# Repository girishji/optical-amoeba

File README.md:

# optical-amoeba
Single switch PCB for Gateron MX-style optical switches

See [pcb](https://github.com/girishji/optical-keyboard)

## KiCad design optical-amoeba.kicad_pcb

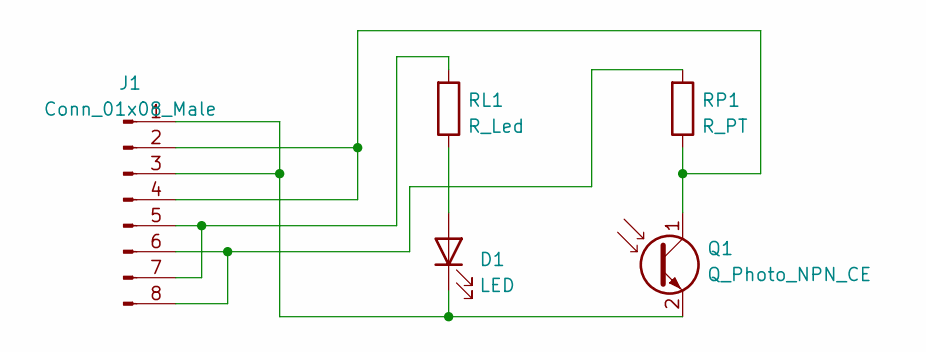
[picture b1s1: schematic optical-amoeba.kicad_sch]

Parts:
D1: LED; Everlight_IR_IR12-21C_TR8; JLC SMD_1.0x3.0x2.0
J1: Conn_01x08_Male; Gateron_Optical_Switch
Q1: Q_Photo_NPN_CE; Everlight_PT_PT12-21C_TR8; JLC SMD_1.0x3.0x2.0
RL1: R_Led; R_0603_1608Metric; JLC 0603-1608
RP1: R_PT; R_0805_2012Metric; JLC 0805-2012

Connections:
unnamed: D1.1 (K), J1.1, J1.3, Q1.2 (E)
unnamed: D1.2 (A), RL1.2
unnamed: J1.2, J1.4, Q1.1 (C), RP1.2
unnamed: J1.5, J1.7, RL1.1
unnamed: J1.6, J1.8, RP1.1

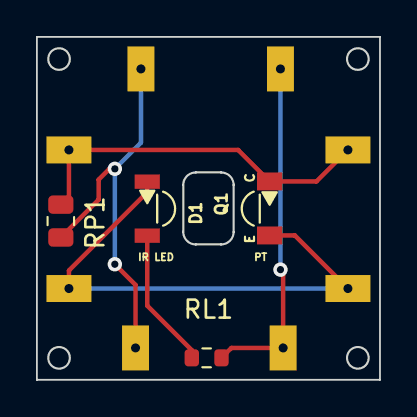
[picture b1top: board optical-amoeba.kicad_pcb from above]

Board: 2 copper layers, 19.1 x 19.0 mm, 5 parts (0 on the bottom side), 5 nets.

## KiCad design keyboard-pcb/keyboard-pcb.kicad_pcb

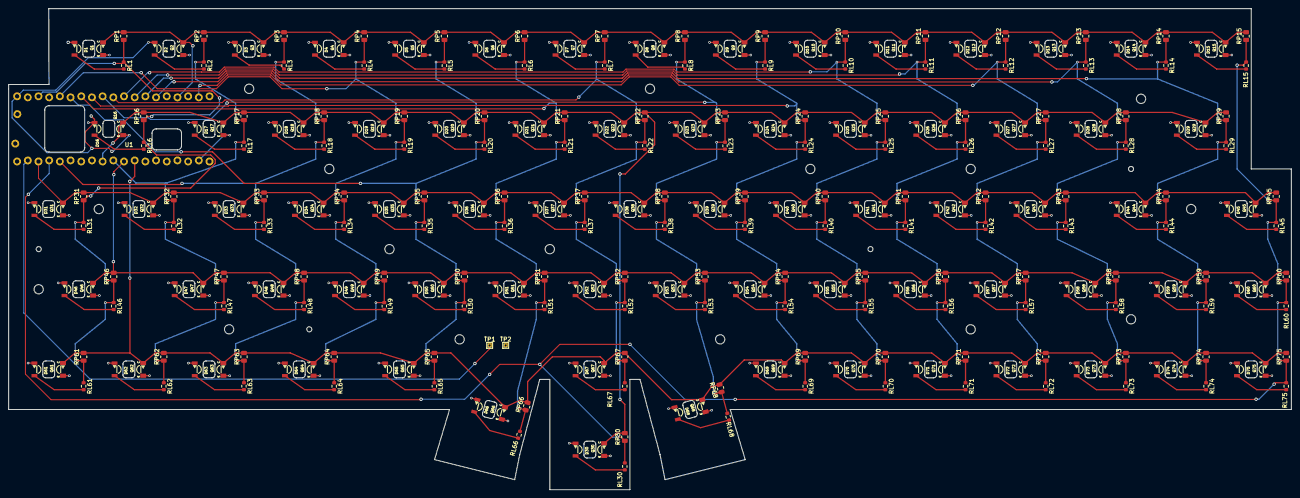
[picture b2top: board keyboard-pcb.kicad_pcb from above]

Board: 2 copper layers, 304.8 x 114.3 mm, 378 parts (0 on the bottom side), 97 nets.

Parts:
D1, D2, D3, D4, D5, D6, D7, D8, D9, D10, D11, D12, D13, D14, D15, D16, D17, D18, D19, D20, D21, D22, D23, D24, D25, D26, D27, D28, D29, D30, D31, D32, D33, D34, D35, D36, D37, D38, D39, D40, D41, D42, D43, D44, D45, D46, D47, D48, D49, D50, D51, D52, D53, D54, D55, D56, D57, D58, D59, D60, D61, D62, D63, D64, D65, D66, D67, D68, D69, D70, D71, D72, D73, D74, D75: IR_LED; Everlight_IR_IR12-21C_TR8
Q1, Q2, Q3, Q4, Q5, Q6, Q7, Q8, Q9, Q10, Q11, Q12, Q13, Q14, Q15, Q16, Q17, Q18, Q19, Q20, Q21, Q22, Q23, Q24, Q25, Q26, Q27, Q28, Q29, Q30, Q31, Q32, Q33, Q34, Q35, Q36, Q37, Q38, Q39, Q40, Q41, Q42, Q43, Q44, Q45, Q46, Q47, Q48, Q49, Q50, Q51, Q52, Q53, Q54, Q55, Q56, Q57, Q58, Q59, Q60, Q61, Q62, Q63, Q64, Q65, Q66, Q67, Q68, Q69, Q70, Q71, Q72, Q73, Q74, Q75: Q_Photo_NPN; Everlight_PT_PT12-21C_TR8
RL1, RL2, RL3, RL4, RL5, RL6, RL7, RL8, RL9, RL10, RL11, RL12, RL13, RL14, RL15, RL16, RL17, RL18, RL19, RL20, RL21, RL22, RL23, RL24, RL25, RL26, RL27, RL28, RL29, RL30, RL31, RL32, RL33, RL34, RL35, RL36, RL37, RL38, RL39, RL40, RL41, RL42, RL43, RL44, RL45, RL46, RL47, RL48, RL49, RL50, RL51, RL52, RL53, RL54, RL55, RL56, RL57, RL58, RL59, RL60, RL61, RL62, RL63, RL64, RL65, RL66, RL67, RL68, RL69, RL70, RL71, RL72, RL73, RL74, RL75: R_Led; R_0603_1608Metric
RP1, RP2, RP3, RP4, RP5, RP6, RP7, RP8, RP9, RP10, RP11, RP12, RP13, RP14, RP15, RP16, RP17, RP18, RP19, RP20, RP21, RP22, RP23, RP24, RP25, RP26, RP27, RP28, RP29, RP30, RP31, RP32, RP33, RP34, RP35, RP36, RP37, RP38, RP39, RP40, RP41, RP42, RP43, RP44, RP45, RP46, RP47, RP48, RP49, RP50, RP51, RP52, RP53, RP54, RP55, RP56, RP57, RP58, RP59, RP60, RP61, RP62, RP63, RP64, RP65, RP66, RP67, RP68, RP69, RP70, RP71, RP72, RP73, RP74, RP75: R_PT; R_0805_2012Metric
S1, S2, S3, S4, S5, S6, S7, S8, S9, S10, S11, S12, S13, S14, S15, S16, S17, S18, S19, S20, S21, S22, S23, S24, S25, S26, S27, S28, S29, S30, S31, S32, S33, S34, S35, S36, S37, S38, S39, S40, S41, S42, S43, S44, S45, S46, S47, S48, S49, S50, S51, S52, S53, S54, S55, S56, S57, S58, S59, S60, S61, S62, S63, S64, S65, S66, S67, S68, S69, S70, S71, S72, S73, S74, S75: Gateron_Optical; Gateron_Switch_Basic
TP1, TP2: TestPoint; TestPoint_THTPad_1.0x1.0mm_Drill0.5mm
U1: BlackPill; BlackPill_STLINK

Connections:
/Capslock_Led: TP1.1, U1.3 (PB14)
/col1: RL1.1, RL16.1, RL31.1, RL46.1, RL61.1, RP1.1, RP16.1, RP31.1, RP46.1, RP61.1, U1.37 (PB10)
/col2: RL2.1, RL17.1, RL32.1, RL47.1, RL62.1, RP2.1, RP17.1, RP32.1, RP47.1, RP62.1, U1.11 (PB3)
/col3: RL3.1, RL18.1, RL33.1, RL48.1, RL63.1, RP3.1, RP18.1, RP33.1, RP48.1, RP63.1, U1.6 (PA9)
/col4: RL4.1, RL19.1, RL34.1, RL49.1, RL64.1, RP4.1, RP19.1, RP34.1, RP49.1, RP64.1, U1.35 (PB1)
/col5: RL5.1, RL20.1, RL35.1, RL50.1, RL65.1, RP5.1, RP20.1, RP35.1, RP50.1, RP65.1, U1.34 (PB0)
/col6: RL6.1, RL21.1, RL36.1, RL51.1, RL66.1, RP6.1, RP21.1, RP36.1, RP51.1, RP66.1, U1.33 (PA7)
/col7: RL9.1, RL24.1, RL39.1, RL54.1, RL69.1, RP9.1, RP24.1, RP39.1, RP54.1, RP69.1, U1.32 (PA6)
/col8: RL8.1, RL23.1, RL38.1, RL53.1, RL68.1, RP8.1, RP23.1, RP38.1, RP53.1, RP68.1, U1.31 (PA5)
/col9: RL7.1, RL22.1, RL37.1, RL52.1, RL67.1, RP7.1, RP22.1, RP37.1, RP52.1, RP67.1, U1.30 (PA4)
/col10: RL10.1, RL25.1, RL40.1, RL55.1, RL70.1, RP10.1, RP25.1, RP40.1, RP55.1, RP70.1, U1.29 (PA3)
/col11: RL11.1, RL26.1, RL41.1, RL56.1, RL71.1, RP11.1, RP26.1, RP41.1, RP56.1, RP71.1, U1.28 (PA2)
/col12: RL14.1, RL29.1, RL44.1, RL59.1, RL74.1, RP14.1, RP29.1, RP44.1, RP59.1, RP74.1, U1.27 (PA1)
/col13: RL13.1, RL28.1, RL43.1, RL58.1, RL73.1, RP13.1, RP28.1, RP43.1, RP58.1, RP73.1, U1.26 (PA0)
/col14: RL12.1, RL27.1, RL42.1, RL57.1, RL72.1, RP12.1, RP27.1, RP42.1, RP57.1, RP72.1, U1.22 (PC13)
/col15: RL15.1, RL30.1, RL45.1, RL60.1, RL75.1, RP15.1, RP30.1, RP45.1, RP60.1, RP75.1, U1.5 (PA8)
/row1: Q1.1 (C), Q2.1 (C), Q3.1 (C), Q4.1 (C), Q5.1 (C), Q6.1 (C), Q7.1 (C), Q8.1 (C), Q9.1 (C), Q10.1 (C), Q11.1 (C), Q12.1 (C), Q13.1 (C), Q14.1 (C), Q15.1 (C), RP1.2, RP2.2, RP3.2, RP4.2, RP5.2, RP6.2, RP7.2, RP8.2, RP9.2, RP10.2, RP11.2, RP12.2, RP13.2, RP14.2, RP15.2, U1.24 (PC15)
/row2: Q16.1 (C), Q17.1 (C), Q18.1 (C), Q19.1 (C), Q20.1 (C), Q21.1 (C), Q22.1 (C), Q23.1 (C), Q24.1 (C), Q25.1 (C), Q26.1 (C), Q27.1 (C), Q28.1 (C), Q29.1 (C), Q30.1 (C), RP16.2, RP17.2, RP18.2, RP19.2, RP20.2, RP21.2, RP22.2, RP23.2, RP24.2, RP25.2, RP26.2, RP27.2, RP28.2, RP29.2, RP30.2, U1.10 (PA15)
/row3: Q31.1 (C), Q32.1 (C), Q33.1 (C), Q34.1 (C), Q35.1 (C), Q36.1 (C), Q37.1 (C), Q38.1 (C), Q39.1 (C), Q40.1 (C), Q41.1 (C), Q42.1 (C), Q43.1 (C), Q44.1 (C), Q45.1 (C), RP31.2, RP32.2, RP33.2, RP34.2, RP35.2, RP36.2, RP37.2, RP38.2, RP39.2, RP40.2, RP41.2, RP42.2, RP43.2, RP44.2, RP45.2, U1.4 (PB15)
/row4: Q46.1 (C), Q47.1 (C), Q48.1 (C), Q49.1 (C), Q50.1 (C), Q51.1 (C), Q52.1 (C), Q53.1 (C), Q54.1 (C), Q55.1 (C), Q56.1 (C), Q57.1 (C), Q58.1 (C), Q59.1 (C), Q60.1 (C), RP46.2, RP47.2, RP48.2, RP49.2, RP50.2, RP51.2, RP52.2, RP53.2, RP54.2, RP55.2, RP56.2, RP57.2, RP58.2, RP59.2, RP60.2, U1.12 (PB4)
/row5: Q61.1 (C), Q62.1 (C), Q63.1 (C), Q64.1 (C), Q65.1 (C), Q66.1 (C), Q67.1 (C), Q68.1 (C), Q69.1 (C), Q70.1 (C), Q71.1 (C), Q72.1 (C), Q73.1 (C), Q74.1 (C), Q75.1 (C), RP61.2, RP62.2, RP63.2, RP64.2, RP65.2, RP66.2, RP67.2, RP68.2, RP69.2, RP70.2, RP71.2, RP72.2, RP73.2, RP74.2, RP75.2, U1.13 (PB5)
GND: D1.1 (K), D2.1 (K), D3.1 (K), D4.1 (K), D5.1 (K), D6.1 (K), D7.1 (K), D8.1 (K), D9.1 (K), D10.1 (K), D11.1 (K), D12.1 (K), D13.1 (K), D14.1 (K), D15.1 (K), D16.1 (K), D17.1 (K), D18.1 (K), D19.1 (K), D20.1 (K), D21.1 (K), D22.1 (K), D23.1 (K), D24.1 (K), D25.1 (K), D26.1 (K), D27.1 (K), D28.1 (K), D29.1 (K), D30.1 (K), D31.1 (K), D32.1 (K), D33.1 (K), D34.1 (K), D35.1 (K), D36.1 (K), D37.1 (K), D38.1 (K), D39.1 (K), D40.1 (K), D41.1 (K), D42.1 (K), D43.1 (K), D44.1 (K), D45.1 (K), D46.1 (K), D47.1 (K), D48.1 (K), D49.1 (K), D50.1 (K), D51.1 (K), D52.1 (K), D53.1 (K), D54.1 (K), D55.1 (K), D56.1 (K), D57.1 (K), D58.1 (K), D59.1 (K), D60.1 (K), D61.1 (K), D62.1 (K), D63.1 (K), D64.1 (K), D65.1 (K), D66.1 (K), D67.1 (K), D68.1 (K), D69.1 (K), D70.1 (K), D71.1 (K), D72.1 (K), D73.1 (K), D74.1 (K), D75.1 (K), Q1.2 (E), Q2.2 (E), Q3.2 (E), Q4.2 (E), Q5.2 (E), Q6.2 (E), Q7.2 (E), Q8.2 (E), Q9.2 (E), Q10.2 (E), Q11.2 (E), Q12.2 (E), Q13.2 (E), Q14.2 (E), Q15.2 (E), Q16.2 (E), Q17.2 (E), Q18.2 (E), Q19.2 (E), Q20.2 (E), Q21.2 (E), Q22.2 (E), Q23.2 (E), Q24.2 (E), Q25.2 (E), Q26.2 (E), Q27.2 (E), Q28.2 (E), Q29.2 (E), Q30.2 (E), Q31.2 (E), Q32.2 (E), Q33.2 (E), Q34.2 (E), Q35.2 (E), Q36.2 (E), Q37.2 (E), Q38.2 (E), Q39.2 (E), Q40.2 (E), Q41.2 (E), Q42.2 (E), Q43.2 (E), Q44.2 (E), Q45.2 (E), Q46.2 (E), Q47.2 (E), Q48.2 (E), Q49.2 (E), Q50.2 (E), Q51.2 (E), Q52.2 (E), Q53.2 (E), Q54.2 (E), Q55.2 (E), Q56.2 (E), Q57.2 (E), Q58.2 (E), Q59.2 (E), Q60.2 (E), Q61.2 (E), Q62.2 (E), Q63.2 (E), Q64.2 (E), Q65.2 (E), Q66.2 (E), Q67.2 (E), Q68.2 (E), Q69.2 (E), Q70.2 (E), Q71.2 (E), Q72.2 (E), Q73.2 (E), Q74.2 (E), Q75.2 (E), TP2.1, U1.19 (GND), U1.39 (GND), U1.44 (GND)
unnamed: D1.2 (A), RL1.2
unnamed: D2.2 (A), RL2.2
unnamed: D3.2 (A), RL3.2
unnamed: D4.2 (A), RL4.2
unnamed: D5.2 (A), RL5.2
unnamed: D6.2 (A), RL6.2
unnamed: D7.2 (A), RL7.2
unnamed: D8.2 (A), RL8.2
unnamed: D9.2 (A), RL9.2
unnamed: D10.2 (A), RL10.2
unnamed: D11.2 (A), RL11.2
unnamed: D12.2 (A), RL12.2
unnamed: D13.2 (A), RL13.2
unnamed: D14.2 (A), RL14.2
unnamed: D15.2 (A), RL15.2
unnamed: D16.2 (A), RL16.2
unnamed: D17.2 (A), RL17.2
unnamed: D18.2 (A), RL18.2
unnamed: D19.2 (A), RL19.2
unnamed: D20.2 (A), RL20.2
unnamed: D21.2 (A), RL21.2
unnamed: D22.2 (A), RL22.2
unnamed: D23.2 (A), RL23.2
unnamed: D24.2 (A), RL24.2
unnamed: D25.2 (A), RL25.2
unnamed: D26.2 (A), RL26.2
unnamed: D27.2 (A), RL27.2
unnamed: D28.2 (A), RL28.2
unnamed: D29.2 (A), RL29.2
unnamed: D30.2 (A), RL30.2
unnamed: D31.2 (A), RL31.2
unnamed: D32.2 (A), RL32.2
unnamed: D33.2 (A), RL33.2
unnamed: D34.2 (A), RL34.2
unnamed: D35.2 (A), RL35.2
unnamed: D36.2 (A), RL36.2
unnamed: D37.2 (A), RL37.2
unnamed: D38.2 (A), RL38.2
unnamed: D39.2 (A), RL39.2
unnamed: D40.2 (A), RL40.2
unnamed: D41.2 (A), RL41.2
unnamed: D42.2 (A), RL42.2
unnamed: D43.2 (A), RL43.2
unnamed: D44.2 (A), RL44.2
unnamed: D45.2 (A), RL45.2
unnamed: D46.2 (A), RL46.2
unnamed: D47.2 (A), RL47.2
unnamed: D48.2 (A), RL48.2
unnamed: D49.2 (A), RL49.2
unnamed: D50.2 (A), RL50.2
unnamed: D51.2 (A), RL51.2
unnamed: D52.2 (A), RL52.2
unnamed: D53.2 (A), RL53.2
unnamed: D54.2 (A), RL54.2
unnamed: D55.2 (A), RL55.2
unnamed: D56.2 (A), RL56.2
unnamed: D57.2 (A), RL57.2
unnamed: D58.2 (A), RL58.2
unnamed: D59.2 (A), RL59.2
unnamed: D60.2 (A), RL60.2
unnamed: D61.2 (A), RL61.2
unnamed: D62.2 (A), RL62.2
unnamed: D63.2 (A), RL63.2
unnamed: D64.2 (A), RL64.2
unnamed: D65.2 (A), RL65.2
unnamed: D66.2 (A), RL66.2
unnamed: D67.2 (A), RL67.2
unnamed: D68.2 (A), RL68.2
unnamed: D69.2 (A), RL69.2
unnamed: D70.2 (A), RL70.2
unnamed: D71.2 (A), RL71.2
unnamed: D72.2 (A), RL72.2
unnamed: D73.2 (A), RL73.2
unnamed: D74.2 (A), RL74.2
unnamed: D75.2 (A), RL75.2

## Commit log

2022-06-03 Initial commit
    M .gitignore
    A Optical_Parts.pretty/Everlight_IR_IR12-21C_TR8.kicad_mod
    A Optical_Parts.pretty/Everlight_PT_PT12-21C_TR8.kicad_mod
    A Optical_Parts.pretty/Gateron_Optical_Switch.kicad_mod
    A Optical_Parts.pretty/MountingHole_1.2mm_M1.kicad_mod
    A Optical_Parts.pretty/TestPoint_THTPad_1.0x1.5mm_Drill0.5mm.kicad_mod
2022-06-10 Added PCB for full keyboard
    M .gitignore
    A OpticalSymbols_Library.kicad_sym
    A Optical_Parts.pretty/BlackPill_STLINK.kicad_mod
    M Optical_Parts.pretty/Everlight_IR_IR12-21C_TR8.kicad_mod
    M Optical_Parts.pretty/Everlight_PT_PT12-21C_TR8.kicad_mod
    M Optical_Parts.pretty/Gateron_Optical_Switch.kicad_mod
2022-06-13 Fixed outlines of edgecuts
    M .gitignore
    A Optical_Parts.pretty/MountingHole_2.2mm_M2.kicad_mod
    M keyboard-pcb/keyboard-pcb.kicad_pcb
    M keyboard-pcb/keyboard-pcb.kicad_prl
    M switch-cutout/switch-cutout.kicad_pcb
    M switch-cutout/switch-cutout.kicad_prl
2022-06-13 gitignore
    M .gitignore
2022-07-19 moved pcb to its own repository
    M OpticalSymbols_Library.kicad_sym
    M Optical_Parts.pretty/BlackPill_STLINK.kicad_mod
    A Optical_Parts.pretty/BlackPill_STLINK2.kicad_mod
    M Optical_Parts.pretty/Gateron_Switch_Basic.kicad_mod
    A Optical_Parts.pretty/MountingHole_2.2mm_M2_jlcpcb.kicad_mod
    A Optical_Parts.pretty/TestPoint_Plated_Hole_D1.2mm.kicad_mod
2022-07-30 Added footprints
    M Optical_Parts.pretty/BlackPill_STLINK.kicad_mod
    M Optical_Parts.pretty/BlackPill_STLINK2.kicad_mod
    M Optical_Parts.pretty/Everlight_IR_IR12-21C_TR8.kicad_mod
    M Optical_Parts.pretty/Everlight_PT_PT12-21C_TR8.kicad_mod
    M Optical_Parts.pretty/Gateron_Optical_Switch.kicad_mod
    M Optical_Parts.pretty/MountingHole_2.2mm_M2_jlcpcb.kicad_mod
2022-07-31 Separated power sourcde for PT and Led
    Having same power source necessiates a diode; Diode degrades
    performance at read pin
    M OpticalSymbols_Library.kicad_sym
    M Optical_Parts.pretty/Gateron_Optical_Switch.kicad_mod
    M optical-amoeba.kicad_pcb
    M optical-amoeba.kicad_prl
2022-08-03 Moved footprints to optical keyboard dir
    M Optical_Parts.pretty/BlackPill_STLINK2.kicad_mod
    D Optical_Parts.pretty/Switch_Cutout.kicad_mod
    D Optical_Parts.pretty/Switch_Cutout_1.25u.kicad_mod
    D Optical_Parts.pretty/Switch_Cutout_1.5u.kicad_mod
    D Optical_Parts.pretty/Switch_Cutout_1.75u.kicad_mod
2022-08-03 Add jlcpcb gerber and assembly files
    M OpticalSymbols_Library.kicad_sym
    A jlcpcb/gerber/optical-amoeba-B_Cu.gbl
    A jlcpcb/gerber/optical-amoeba-B_Mask.gbs
    A jlcpcb/gerber/optical-amoeba-B_Paste.gbp
    A jlcpcb/gerber/optical-amoeba-B_Silkscreen.gbo
    A jlcpcb/gerber/optical-amoeba-Edge_Cuts.gm1
2022-08-03 Add assembly files
    M .gitignore
    A jlcpcb/assembly/optical-amoeba-BOM.csv
    A jlcpcb/assembly/optical-amoeba-top-pos.csv
